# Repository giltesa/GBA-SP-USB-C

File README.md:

# Game Boy Advance SP USB-C & Audio Kit

This board allows to replace the original EXT2 connector and keep both original features: You can charge the GBASP by USB-C and **connect to your headphones to hear the games**!

## Youtube:

Game Boy Advance SP USB-C & Audio Kit (Installation)

## Would you like it?

https://shop.giltesa.com/product/game-boy-advance-sp-usb-c-kit/

https://shop.giltesa.com/product/game-boy-advance-sp-usb-c-kit-centered/

## More

- [giltesa.com](https://giltesa.com "giltesa.com")
- [twitter.com](https://twitter.com/giltesa/status/1503669454852481024 "twitter.com")

## Thanks

Thanks to these makers for publishing the information about the pinout and their experiences, it helped me to make this board:

[ishoug](https://www.youtube.com/watch?v=KATEinUUWz0 "ishoug")

[666Gothicgirl](https://www.youtube.com/watch?v=5_2sGFCsaPw "666Gothicgirl")

## License

This project is licensed under a **Creative Commons** license:
**[Attribution-NonCommercial-ShareAlike 4.0 International (CC BY-NC-SA 4.0) ](https://creativecommons.org/licenses/by-nc-sa/4.0/)**

Check the [LICENSE.md](LICENSE.md) for more information.

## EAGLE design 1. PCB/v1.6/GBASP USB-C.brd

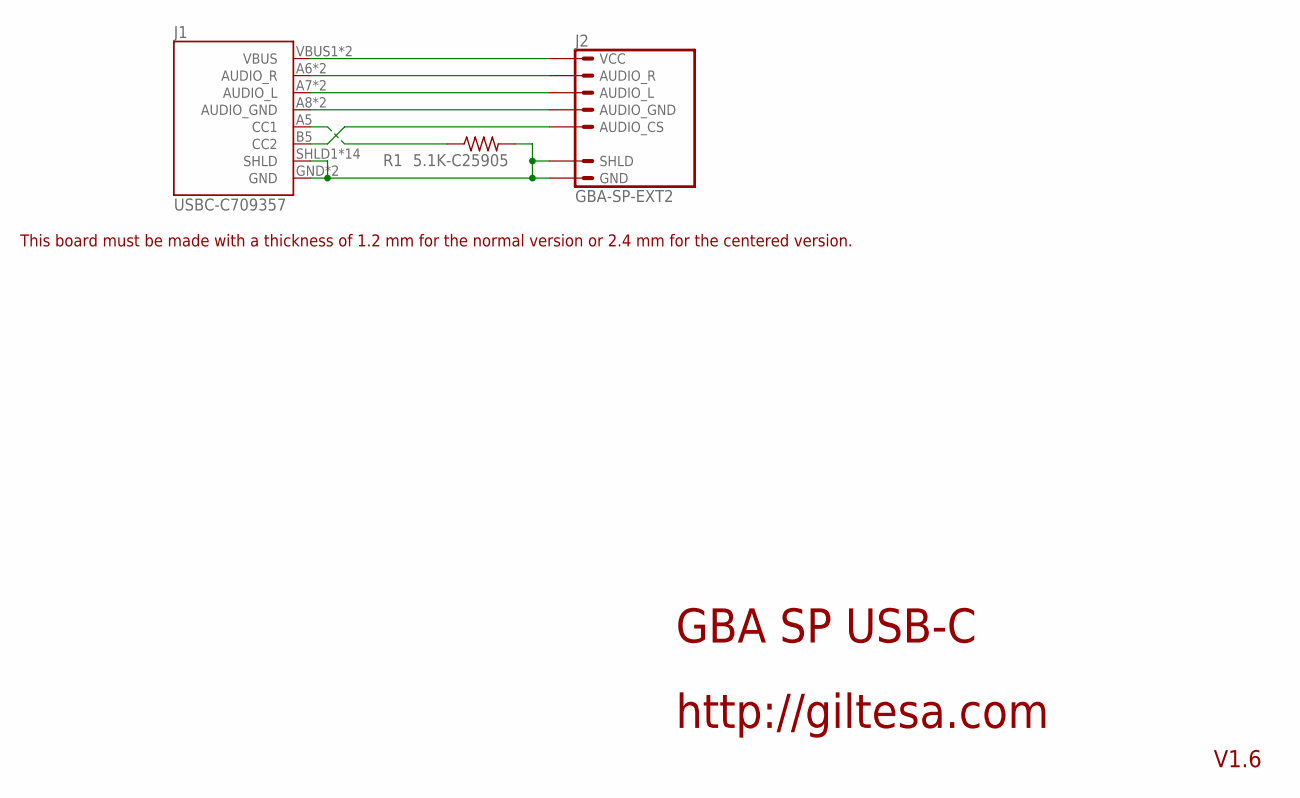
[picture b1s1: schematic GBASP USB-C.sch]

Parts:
J1: USBC-C709357; USB-C_16P_3SHLD_DRILL
J2: GBA-SP-EXT2; GBA-SP-EXT2_1
R1: 5.1K-C25905; R0402

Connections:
AUDIO_GND: J1.A8 (AUDIO_GND), J1.B8 (AUDIO_GND), J2.AUDIO_GND
AUDIO_L: J1.A7 (AUDIO_L), J1.B7 (AUDIO_L), J2.AUDIO_L
AUDIO_R: J1.A6 (AUDIO_R), J1.B6 (AUDIO_R), J2.AUDIO_R
CC2: J1.B5 (CC2), J2.AUDIO_CS
GND: J1.GND, J1.GND2 (GND), J1.SHLD1 (SHLD), J1.SHLD1_2 (SHLD), J1.SHLD3 (SHLD), J1.SHLD3_2 (SHLD), J1.SHLD4 (SHLD), J1.SHLD4_2 (SHLD), J1.SHLD5 (SHLD), J1.SHLD5_2 (SHLD), J1.SHLD6 (SHLD), J1.SHLD6_2 (SHLD), J1.SHLD7 (SHLD), J1.SHLD7_2 (SHLD), J1.SHLD8 (SHLD), J1.SHLD8_2 (SHLD), J2.GND, J2.SHLD1 (SHLD), J2.SHLD2 (SHLD), J2.SHLD3 (SHLD), J2.SHLD4 (SHLD), R1.2
unnamed: J1.A5 (CC1), R1.1
VCC: J1.VBUS1 (VBUS), J1.VBUS2 (VBUS), J2.VCC

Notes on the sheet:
GBA SP USB-C
http://giltesa.com
V1.6
This board must be made with a thickness of 1.2 mm for the normal version or 2.4 mm for the centered version.

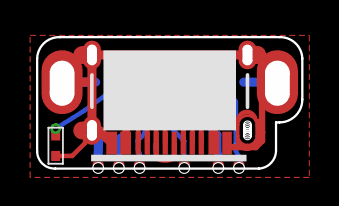
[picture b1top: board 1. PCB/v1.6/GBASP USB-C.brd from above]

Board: 2 copper layers, 13.5 x 6.1 mm, 3 parts (0 on the bottom side), 7 nets.

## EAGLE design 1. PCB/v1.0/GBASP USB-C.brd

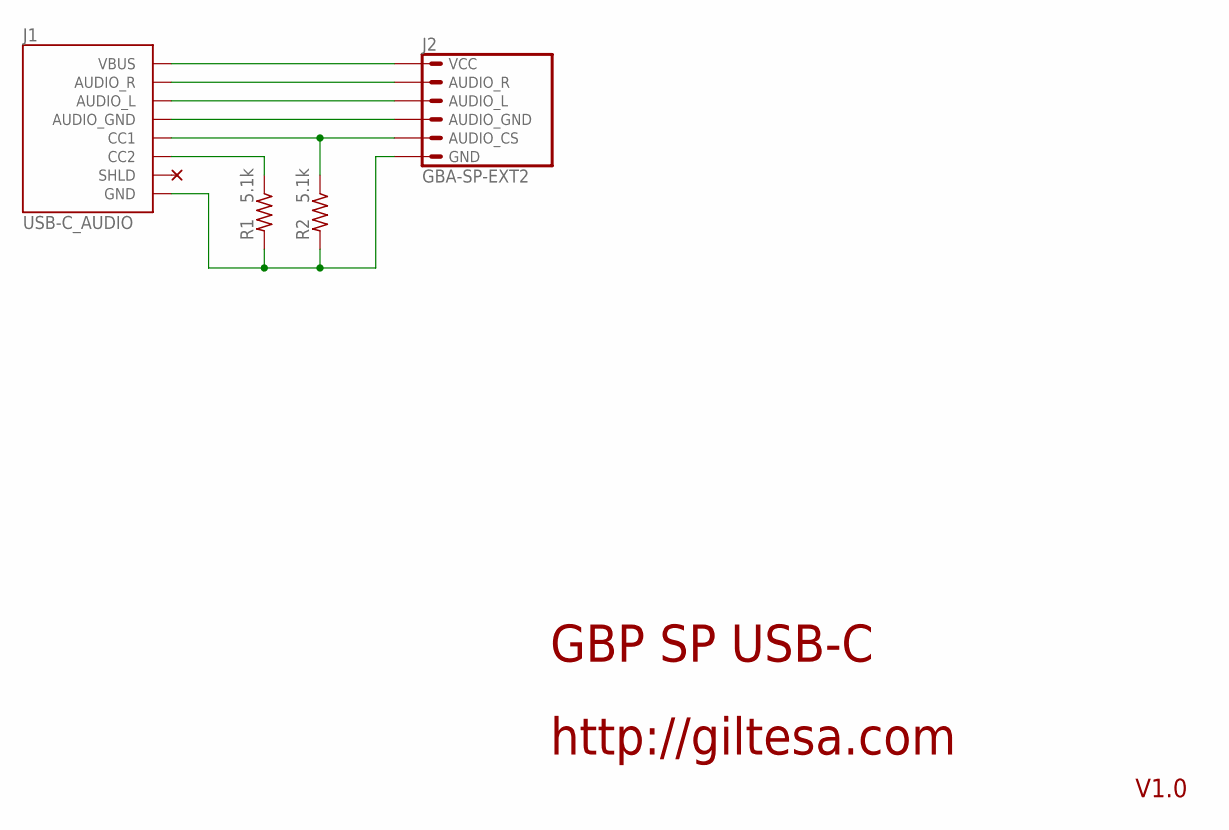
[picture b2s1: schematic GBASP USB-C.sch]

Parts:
J1: USB-C_AUDIO; USB-C_16P_SHLD2
J2: GBA-SP-EXT2
R1, R2: 5.1k; R0402

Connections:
AUDIO_GND: J1.A8 (AUDIO_GND), J1.B8 (AUDIO_GND), J2.AUDIO_GND@1 (AUDIO_GND), J2.AUDIO_GND@2 (AUDIO_GND)
AUDIO_L: J1.A7 (AUDIO_L), J1.B7 (AUDIO_L), J2.AUDIO_L@1 (AUDIO_L), J2.AUDIO_L@2 (AUDIO_L)
AUDIO_R: J1.A6 (AUDIO_R), J1.B6 (AUDIO_R), J2.AUDIO_R@1 (AUDIO_R), J2.AUDIO_R@2 (AUDIO_R)
CC1: J1.A5 (CC1), J2.AUDIO_CS@1 (AUDIO_CS), J2.AUDIO_CS@2 (AUDIO_CS), R2.1
CC2: J1.B5 (CC2), R1.1
GND: J1.GND, J1.GND2 (GND), J2.GND@1 (GND), J2.GND@2 (GND), R1.2, R2.2
VCC: J1.VBUS1 (VBUS), J1.VBUS2 (VBUS), J2.VCC@1 (VCC), J2.VCC@2 (VCC)

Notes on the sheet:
GBP SP USB-C
http://giltesa.com
V1.0

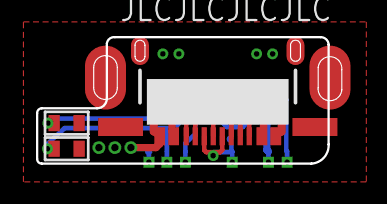
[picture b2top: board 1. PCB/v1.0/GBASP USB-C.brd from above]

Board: 2 copper layers, 16.9 x 7.0 mm, 4 parts (0 on the bottom side), 7 nets.

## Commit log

2021-04-04 no message
2021-06-18 Revert "no message"
    This reverts commit c18211bc541e15862b2848c128a3f8aa5f60c536.
2021-09-14 v1.0
2021-09-14 v1.1
2021-09-14 v1.2
2023-05-10 v1.3
2023-05-10 v1.4
2023-05-10 v1.5
2024-01-15 v1.6
